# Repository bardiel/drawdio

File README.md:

# DRAWDIO 

Eagle schematics for drawdio

## Items

Part    | Value    	| Notes
--------|---------------|-----------------
Q1	| NE555	   	| --
R1	| 270K		| --
R2	| 10K		| --
R3	| 100ohm	| --
C1 	| 680pF		| Ceramic, 5mm
C2	| 0.1µF		| Ceramic, 2.5mm
C3	| 100µF		| Electrolitic, 2.5mm
T1	| 2907A		| PNP Switching transistor

## Notes

I used 12v "A23" battery, but they suck! I'd rather have a cord and a 9v battery.

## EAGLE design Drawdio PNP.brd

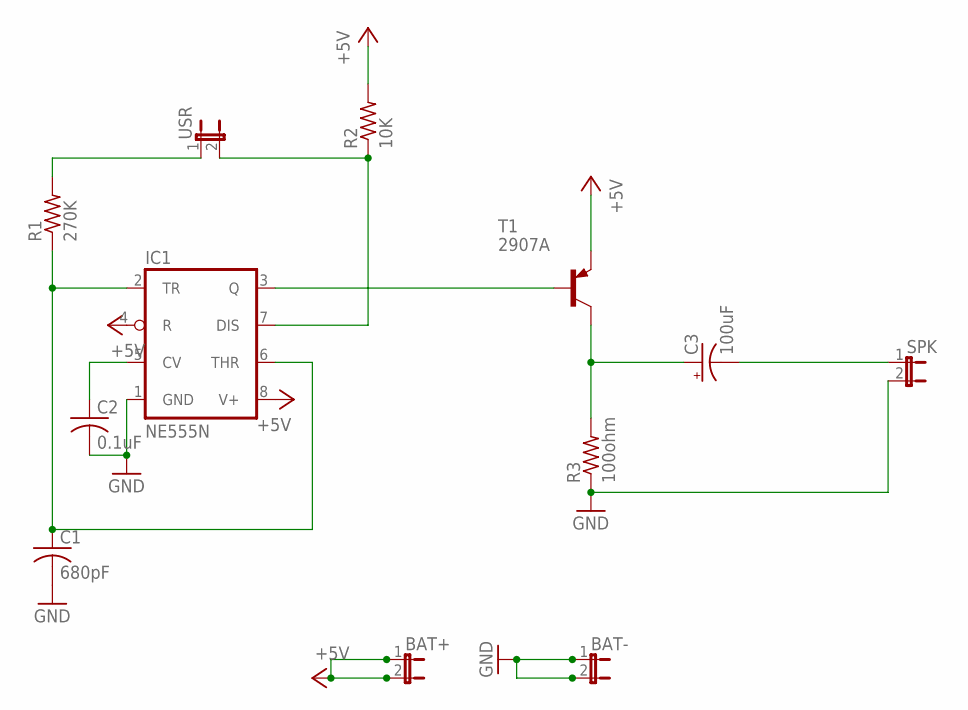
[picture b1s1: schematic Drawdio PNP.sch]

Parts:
BAT+: JP1E; JP1
BAT-: JP1E; JP1
C1: 680pF; C025-025X050
C2: 0.1uF; C050-025X075
C3: 100uF; E2,5-5
IC1: NE555N; DIL08
R1: 270K; 0204/7
R2: 10K; 0204/7
R3: 100ohm; 0204/7
SPK: JP1E; JP1
T1: 2907A; TO92-CBE
USR: JP1E; JP1

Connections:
+5V: BAT+.1, BAT+.2, IC1.4 (R), IC1.8 (V+), R2.2, T1.E
GND: BAT-.1, BAT-.2, C1.2, C2.2, IC1.1 (GND), R3.1, SPK.2
unnamed: R1.2, USR.1
unnamed: IC1.7 (DIS), R2.1, USR.2
unnamed: IC1.3 (Q), T1.B
unnamed: C1.1, IC1.2 (TR), IC1.6 (THR), R1.1
unnamed: C3.+, R3.2, T1.C
unnamed: C3.-, SPK.1
unnamed: C2.1, IC1.5 (CV)

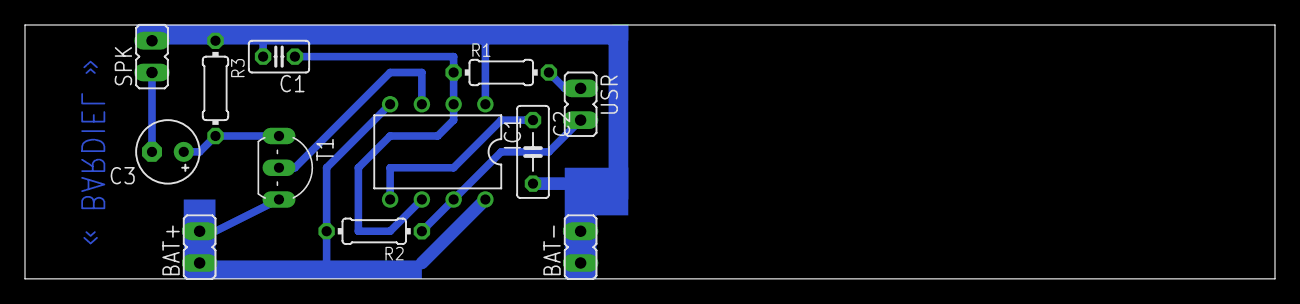
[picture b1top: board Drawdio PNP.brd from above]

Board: 2 copper layers, 100.0 x 20.3 mm, 12 parts (0 on the bottom side), 9 nets.
